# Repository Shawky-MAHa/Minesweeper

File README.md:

This pcb used to control 4 DC motors and 4 SERVO motor.  
this pcb receive 3 ultrasonic sensor for wall detect and one DIY metal detector.  
this pcb receive commands from NRF or ps2 using SPI commnacation protocol.  
this pcb desplay the sensor dectect on LCD using I2C commnacation protocol.  
this pcb can handle 5 Ampere output current using current booster cicuit.  
this pcb have over current protection (FUSE)).  
this pcb use Arduino Mega for control and have a breakout for the arduino.  
the input voltage(24-12)V and the output voltage that you can take is 5v,12V.

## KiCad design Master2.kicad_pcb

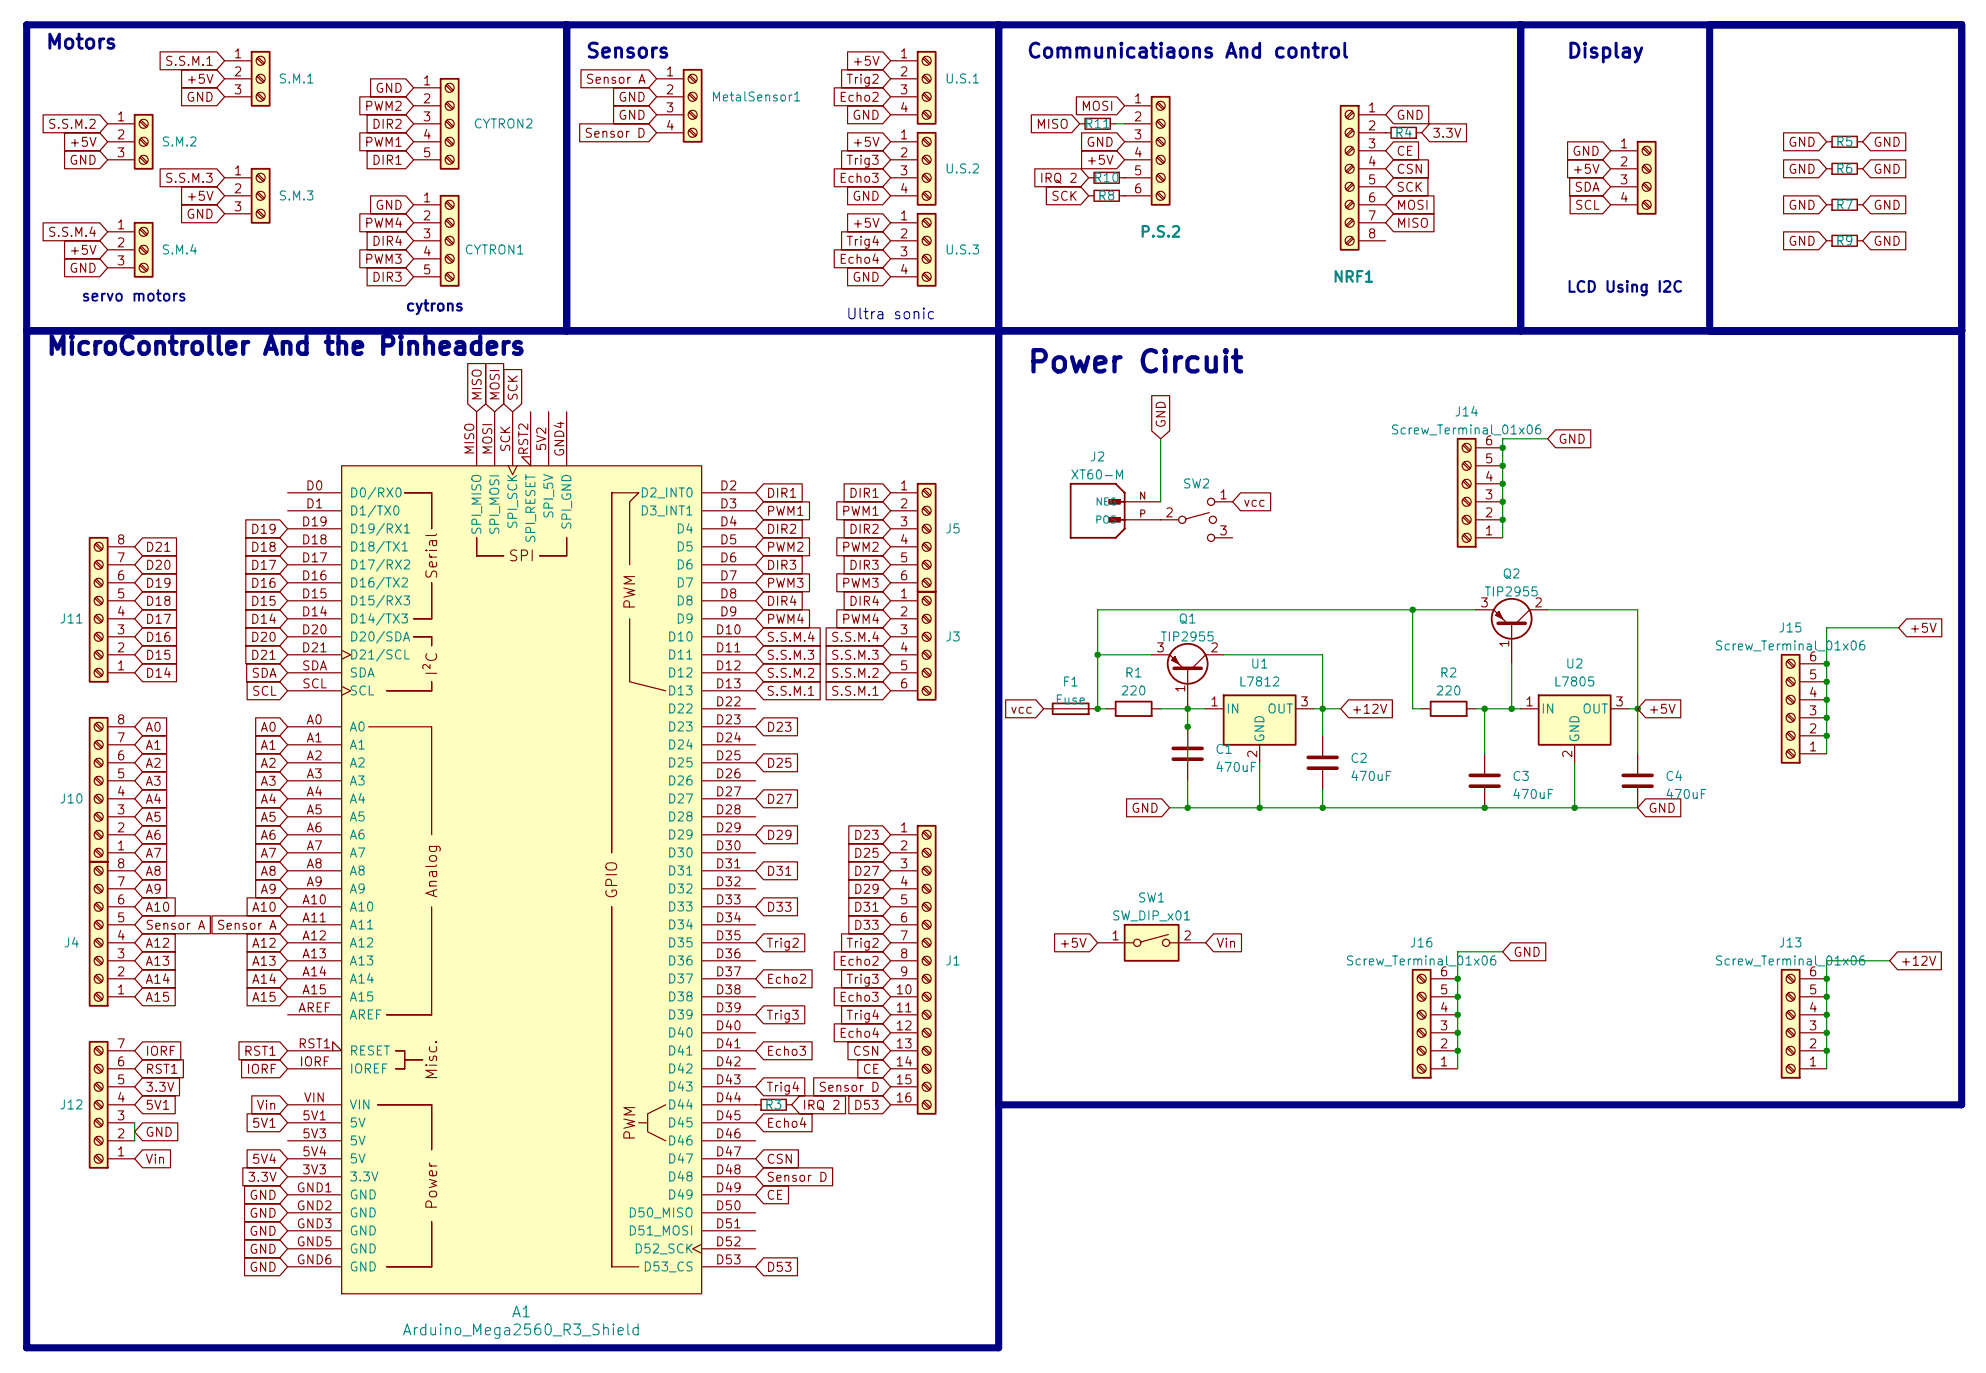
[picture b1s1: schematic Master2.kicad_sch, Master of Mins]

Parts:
A1: Arduino_Mega2560_R3_Shield
C1, C2, C3, C4: 470uF; CP_Radial_D8.0mm_P2.50mm
CYTRON1, CYTRON2: Conn_01x05_Pin; PinSocket_1x05_P2.54mm_Vertical
F1: Fuse; FUSE_4628
J1: Conn_01x16_Socket; PinHeader_1x16_P2.54mm_Vertical
J2: XT60-M; AMASS_XT60-M; PARTREV V1.2
J3: Conn_01x06_Socket; PinHeader_1x06_P2.54mm_Vertical
J4, J10, J11: Conn_01x08_Socket; PinHeader_1x08_P2.54mm_Vertical
J5: Conn_01x08_Socket; PinHeader_1x06_P2.54mm_Vertical
J12: Conn_01x07_Pin; PinHeader_1x07_P2.54mm_Vertical
J13, J14, J15, J16: Screw_Terminal_01x06; Altech_AK300_1x06_P5.00mm_45-Degree
LCD16*2.I2C1: PinHeader_1x04_P2.54mm_Vertical
MetalSensor1: Conn_01x03_Socket; PinHeader_1x04_P2.54mm_Vertical
NRF1: Conn_01x08_Pin; module_vl53l0x
P.S.2: P.S.2; PinHeader_1x06_P2.54mm_Vertical
Q1, Q2: TIP2955; TO-220-3_Vertical
R1, R2: 220; R_Axial_DIN0411_L9.9mm_D3.6mm_P15.24mm_Horizontal
R3, R5, R6, R7, R8: R_Small; R_Axial_DIN0411_L9.9mm_D3.6mm_P15.24mm_Horizontal
R4, R9, R10, R11: R_Small; R_Axial_DIN0207_L6.3mm_D2.5mm_P10.16mm_Horizontal
S.M.1, S.M.2, S.M.3, S.M.4: Conn_01x03_Pin; PinHeader_1x03_P2.54mm_Vertical
SW1: SW_DIP_x01; SW_DIP_SPSTx01_Piano_10.8x4.1mm_W7.62mm_P2.54mm
SW2: SW_SPST; SW_E-Switch_EG1224_SPDT_Angled
U1: L7812; TO-220-3_Vertical
U2: L7805; TO-220-3_Vertical
U.S.1, U.S.2, U.S.3: PinHeader_1x04_P2.54mm_Vertical

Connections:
3.3V: A1.3V3 (3.3V), J12.5, R4.1
5V1: A1.5V1 (5V), J12.4
5V4: A1.5V4 (5V)
+5V: C4.1, J15.1, J15.2, J15.3, J15.4, J15.5, J15.6, LCD16*2.I2C1.2, P.S.2.4, Q2.2 (C), S.M.1.2, S.M.2.2, S.M.3.2, S.M.4.2, SW1.1, U2.3 (OUT), U.S.1.1, U.S.2.1, U.S.3.1
+12V: C2.1, J13.1, J13.2, J13.3, J13.4, J13.5, J13.6, Q1.2 (C), U1.3 (OUT)
A0: A1.A0, J10.8
A1: A1.A1, J10.7
A2: A1.A2, J10.6
A3: A1.A3, J10.5
A4: A1.A4, J10.4
A5: A1.A5, J10.3
A6: A1.A6, J10.2
A7: A1.A7, J10.1
A8: A1.A8, J4.8
A9: A1.A9, J4.7
A10: A1.A10, J4.6
A12: A1.A12, J4.4
A13: A1.A13, J4.3
A14: A1.A14, J4.2
A15: A1.A15, J4.1
CE: A1.D49, J1.14, NRF1.3
CSN: A1.D47, J1.13, NRF1.4
D14: A1.D14 (D14/TX3), J11.1
D15: A1.D15 (D15/RX3), J11.2
D16: A1.D16 (D16/TX2), J11.3
D17: A1.D17 (D17/RX2), J11.4
D18: A1.D18 (D18/TX1), J11.5
D19: A1.D19 (D19/RX1), J11.6
D20: A1.D20 (D20/SDA), J11.7
D21: A1.D21 (D21/SCL), J11.8
D23: A1.D23, J1.1
D25: A1.D25, J1.2
D27: A1.D27, J1.3
D29: A1.D29, J1.4
D31: A1.D31, J1.5
D33: A1.D33, J1.6
D53: A1.D53 (D53_CS), J1.16
DIR1: A1.D2 (D2_INT0), CYTRON2.5, J5.1
DIR2: A1.D4, CYTRON2.3, J5.3
DIR3: A1.D6, CYTRON1.5, J5.5
DIR4: A1.D8, CYTRON1.3, J3.1
Echo2: A1.D37, J1.8, U.S.1.3
Echo3: A1.D41, J1.10, U.S.2.3
Echo4: A1.D45, J1.12, U.S.3.3
GND: A1.GND1 (GND), A1.GND2 (GND), A1.GND3 (GND), A1.GND5 (GND), A1.GND6 (GND), C1.2, C2.2, C3.2, C4.2, CYTRON1.1, CYTRON2.1, J2.N (NEG), J12.2, J12.3, J14.1, J14.2, J14.3, J14.4, J14.5, J14.6, J16.1, J16.2, J16.3, J16.4, J16.5, J16.6, LCD16*2.I2C1.1, MetalSensor1.2, MetalSensor1.3, NRF1.1, P.S.2.3, R5.1, R5.2, R6.1, R6.2, R7.1, R7.2, R9.1, R9.2, S.M.1.3, S.M.2.3, S.M.3.3, S.M.4.3, U1.2 (GND), U2.2 (GND), U.S.1.4, U.S.2.4, U.S.3.4
IORF: A1.IORF (IOREF), J12.7
IRQ 2: R3.2, R10.2
MISO: A1.MISO (SPI_MISO), NRF1.7, R11.2
MOSI: A1.MOSI (SPI_MOSI), NRF1.6, P.S.2.1
unnamed: A1.D44, R3.1
unnamed: J2.P (POS), SW2.2
unnamed: NRF1.2, R4.2
unnamed: P.S.2.2, R11.1
unnamed: P.S.2.5, R10.1
unnamed: P.S.2.6, R8.1
unnamed: C1.1, Q1.1 (B), R1.2, U1.1 (IN)
unnamed: F1.2, Q1.3 (E), Q2.3 (E), R1.1, R2.1
unnamed: C3.1, Q2.1 (B), R2.2, U2.1 (IN)
PWM1: A1.D3 (D3_INT1), CYTRON2.4, J5.2
PWM2: A1.D5, CYTRON2.2, J5.4
PWM3: A1.D7, CYTRON1.4, J5.6
PWM4: A1.D9, CYTRON1.2, J3.2
RST1: A1.RST1 (RESET), J12.6
S.S.M.1: A1.D13, J3.6, S.M.1.1
S.S.M.2: A1.D12, J3.5, S.M.2.1
S.S.M.3: A1.D11, J3.4, S.M.3.1
S.S.M.4: A1.D10, J3.3, S.M.4.1
SCK: A1.SCK (SPI_SCK), NRF1.5, R8.2
SCL: A1.SCL, LCD16*2.I2C1.4
SDA: A1.SDA, LCD16*2.I2C1.3
Sensor A: A1.A11, J4.5, MetalSensor1.1
Sensor D: A1.D48, J1.15, MetalSensor1.4
Trig2: A1.D35, J1.7, U.S.1.2
Trig3: A1.D39, J1.9, U.S.2.2
Trig4: A1.D43, J1.11, U.S.3.2
Vin: A1.VIN, J12.1, SW1.2
vcc: F1.1, SW2.1

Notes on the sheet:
cytrons
MicroController And the Pinheaders
Motors
LCD Using I2C
Sensors
Communicatiaons And control
Ultra sonic
Display
servo motors
Power Circuit

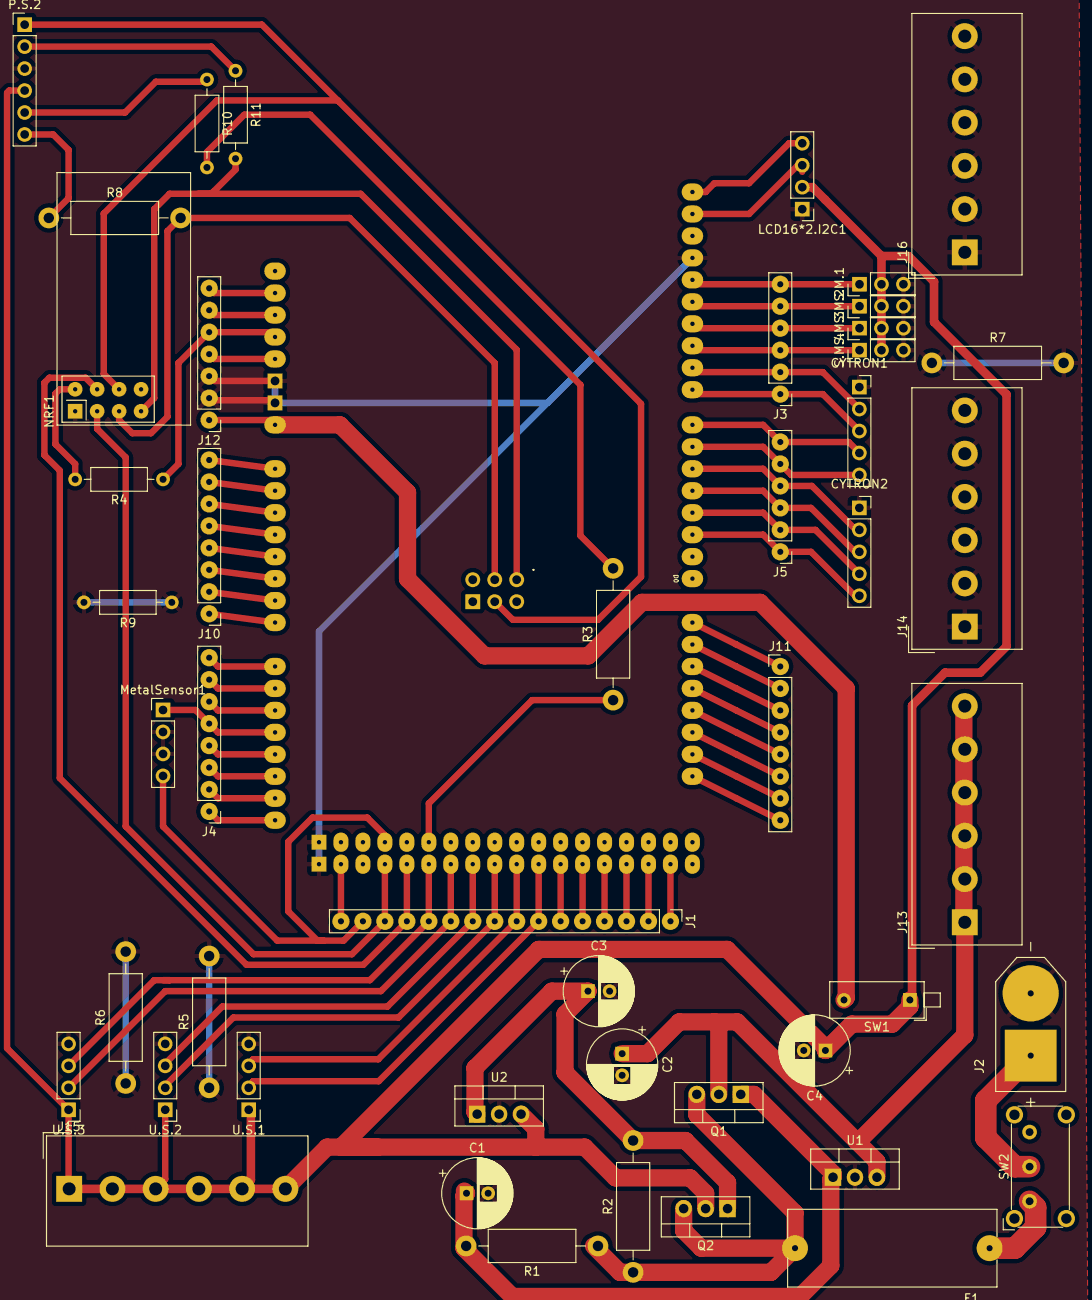
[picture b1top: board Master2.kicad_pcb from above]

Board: 2 copper layers, 48 parts (0 on the bottom side), 76 nets.

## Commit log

2024-05-13 THE master pcb for minesweeper ROBOT 2023
2024-05-14 READ
